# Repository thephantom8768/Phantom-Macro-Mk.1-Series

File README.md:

# Phantom Macro Mk.1 Series

> A modular, snap-together macropad ecosystem with lateral pogo-pin bus interconnects.

Chain modules side-by-side to expand your desktop workflow—from a compact macro-pad into a full fledge keyboard.

---

## 📌 Project Status

- **Hardware:** Series still in-dev
- **Case/Enclosure:** Currently only available for Pad. (Half-life week 2, its inside 3D case file)
- **Firmware:** Pad is almost complete but I need to built it to measure the adc. Others are still in-dev
- **Interconnect:** Custom edge-mount 8 pin pogo interface.

---

## ⚡ Features

- **Snap & Chain Topology:** Expand your layout horizontally by mating adjacent modules using edge-mounted pogo connectors.
- **Unified Bus Standard:** Standardized power, ground, and communication rails allow any Mk.1-series compatible module to hot-mate with the system.
- **Flexible Layouts:** Mix and match different form factors (numpads, macro clusters, encoder dials) without rerunning separate USB cables to your host machine.

## ⚠️ Build Warnings

> [!WARNING]
> **DIY Soldering Required:** This is a fully self-assembled project. It is not a plug-and-play kit and requires intermediate soldering experience.

* **Double-Sided Assembly:** Depending on the macro-pad, components might need to be soldered onto **both the top and bottom** of the PCB.

## *Mk.1 Series*

<details>
  <summary><b>🔢 Phantom-Macro-Mk.1 Pad (click here)</b></summary>
  
  ### Macro Mk.1 Pad
  
  #### Schematic

#### PCB Layout

4 Layers PCB

<div style="width: max; height: max; overflow: hidden; display: inline-block;">
  
</div>

| Front (1st layer) | Bottom (4th layer) |
| ----------------- | ------------------ |
|  |  |
|  |  |

#### PCB
| Front | Back |
| ----- | ---- |
|  |  |
|  |  |

#### Case

<table>
  <tbody>
    <tr>
      <td width="50%">
        
      </td>
      <td width="50%">
        
      </td>
    </tr>
    <tr>
      <td width="50%">
        
      </td>
      <td width="50%">
        
      </td>
    </tr>
  </tbody>
</table>

</details>

<details>
  <summary><b>🎹 Phantom-Macro-Mk.1 MIDI (click here)</b></summary>
  
  ### Macro Mk.1 MIDI
  
  #### Schematic

  #### PCB Layout 

  2 Layers PCB

  | Front | Back |
  | ----- | ----- |
  |  |  |
  |  |  |

  #### PCB
  | Front | Back |
  | ----- | ---- |
  |  |  |
  |  |  |

</details>

<details>
  <summary><b>📱 Phantom-Macro-Mk.1-Prism (click here)</b></summary>

  ### Macro Mk.1 Prism

  #### Schematic

  #### PCB Layout

  4 Layers PCB

  | Front (1st layer) | Bottom (4th layer) |
  | ----------------- | ------------------ |
  | |  |
  | |  |

  #### PCB

  | Front | Back |
  | ----- | ---- |
  | |  |
  | |  |

</details>

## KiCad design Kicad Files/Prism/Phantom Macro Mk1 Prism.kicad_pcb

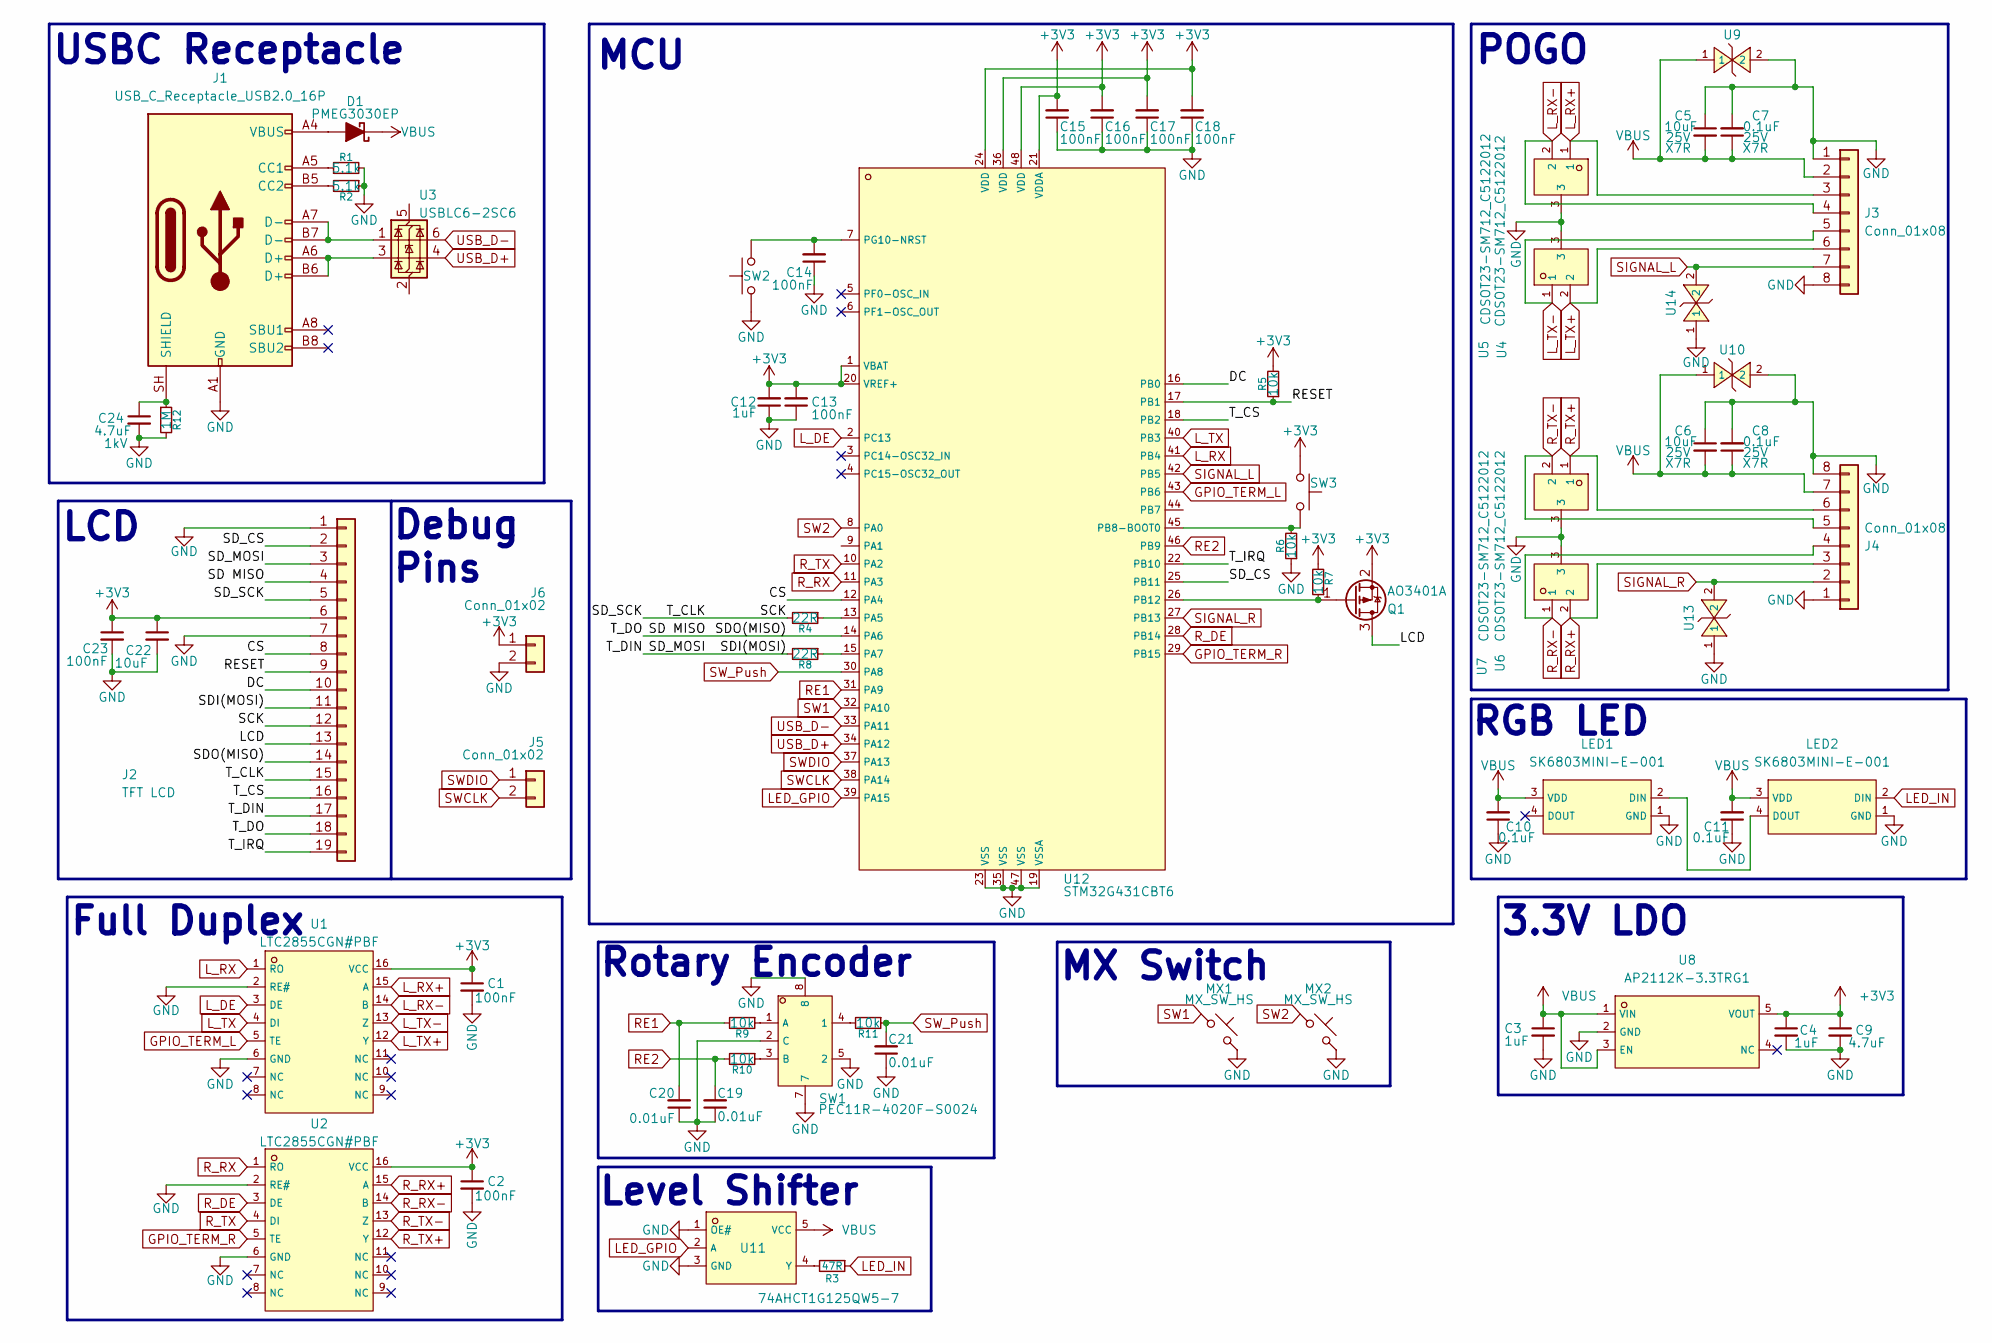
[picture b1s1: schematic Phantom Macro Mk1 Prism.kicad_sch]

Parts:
C1, C2, C13, C14, C15, C16, C17, C18: 100nF; C_0402_1005Metric_Pad0.74x0.62mm_HandSolder
C3, C4, C12: 1uF; C_0603_1608Metric_Pad1.08x0.95mm_HandSolder
C5, C6: 10uF; C_0805_2012Metric_Pad1.18x1.45mm_HandSolder; Rating 25V
C7, C8: 0.1uF; C_0805_2012Metric_Pad1.18x1.45mm_HandSolder; Rating 25V
C9, C24: 4.7uF; C_0805_2012Metric_Pad1.18x1.45mm_HandSolder
C10, C11: 0.1uF; C_0402_1005Metric_Pad0.74x0.62mm_HandSolder
C19, C20, C21: 0.01uF; C_0805_2012Metric_Pad1.18x1.45mm_HandSolder
C22: 10uF; C_0805_2012Metric_Pad1.18x1.45mm_HandSolder
C23: 100nF; C_0805_2012Metric_Pad1.18x1.45mm_HandSolder
D1: PMEG3030EP; D_SOD-128
J1: USB_C_Receptacle_USB2.0_16P; USB_C_Receptacle_GCT_USB4085
J2: TFT LCD; DLS23028B 2.8 inch SPI TFT LCD
J3, J4: Conn_01x08; PinHeader_1x08_P2.54mm_Horizontal
J5, J6: Conn_01x02; PinHeader_1x02_P2.54mm_Vertical
LED1, LED2: SK6803MINI-E-001; C5242955_LED-SMD_4P-L3_2-W2_8_SK6803MINI-E-001; LCSC C5242955
MX1, MX2: MX_SW_HS; SW_MX_HS_CPG151101S11_1u
Q1: AO3401A; SOT-23
R1, R2: 5.1k; R_0402_1005Metric_Pad0.72x0.64mm_HandSolder
R3: 47R; R_0402_1005Metric_Pad0.72x0.64mm_HandSolder
R4, R8: 22R; R_0402_1005Metric_Pad0.72x0.64mm_HandSolder
R5, R6, R7, R9, R10, R11: 10k; R_0402_1005Metric_Pad0.72x0.64mm_HandSolder
R12: 1M; R_0805_2012Metric_Pad1.20x1.40mm_HandSolder
SW1: PEC11R-4020F-S0024; C143788_SW-TH_5P-L12_5-W13_4-P2_50-LS14_5; LCSC C143788
SW2, SW3: SW_Push; SW_SPST_B3U-1000P
U1, U2: LTC2855CGN#PBF; C682796_SSOP-16_L4_9-W3_9-P0_64-LS6_0-BL; LCSC C682796
U3: USBLC6-2SC6; SOT-23-6
U4, U5, U6, U7: CDSOT23-SM712_C5122012; C5122012_SOT-23-3_L2_9-W1_3-P0_95-LS2_4-BR; LCSC C5122012
U8: AP2112K-3.3TRG1; C51118_SOT-25-5_L2_9-W1_6-P0_95-LS2_8-BL; LCSC C51118
U9, U10, U13, U14: TPD1E10B06DPYR; C48260_X1SON-2_L1_0-W0_6-P0_65-BI-1; LCSC C48260
U11: 74AHCT1G125QW5-7; C3755013_SOT-753_L3_1-W1_7-P0_95-LS3_0-BR; LCSC C3755013
U12: STM32G431CBT6; C529355_LQFP-48_L7_0-W7_0-P0_50-LS9_0-BL; LCSC C529355

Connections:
+3V3: C1.1, C2.1, C4.1, C9.1, C12.2, C13.2, C15.2, C16.2, C17.2, C18.2, C22.1, C23.1, J2.6, J6.1, Q1.2 (S), R5.2, R7.2, SW3.2, U1.16 (VCC), U2.16 (VCC), U8.5 (VOUT), U12.1 (VBAT), U12.20 (VREF+), U12.21 (VDDA), U12.24 (VDD), U12.36 (VDD), U12.48 (VDD)
/CS: J2.8, U12.12 (PA4)
/DC: J2.10, U12.16 (PB0)
/LCD: J2.13, Q1.3 (D)
/RESET: J2.9, R5.1, U12.17 (PB1)
/SCK: J2.5, J2.12, J2.15, R4.2
/SD MISO: J2.4, J2.14, J2.18, U12.14 (PA6)
/SDI(MOSI): J2.3, J2.11, J2.17, R8.2
/SD_CS: J2.2, U12.25 (PB11)
/T_CS: J2.16, U12.18 (PB2)
/T_IRQ: J2.19, U12.22 (PB10)
GND: C1.2, C2.2, C3.2, C4.2, C5.1, C6.1, C7.2, C8.2, C9.2, C10.1, C11.1, C12.1, C13.1, C14.1, C15.1, C16.1, C17.1, C18.1, C19.1, C20.1, C21.1, C22.2, C23.2, C24.2, J1.A1 (GND), J1.A12 (GND), J1.B1 (GND), J1.B12 (GND), J2.1, J2.7, J3.1, J3.8, J4.1, J4.8, J6.2, LED1.1 (GND), LED2.1 (GND), MX1.2, MX2.2, R1.2, R2.1, R6.1, R12.2, SW1.2 (C), SW1.5 (2), SW1.7, SW1.8, SW2.1, U1.2 (RE#), U1.6 (GND), U2.2 (RE#), U2.6 (GND), U4.3, U5.3, U6.3, U7.3, U8.2 (GND), U9.2, U10.2, U11.1 (OE#), U11.3 (GND), U12.19 (VSSA), U12.23 (VSS), U12.35 (VSS), U12.47 (VSS), U13.1, U14.1
GPIO_TERM_L: U1.5 (TE), U12.43 (PB6)
GPIO_TERM_R: U2.5 (TE), U12.29 (PB15)
LED_GPIO: U11.2 (A), U12.39 (PA15)
LED_IN: LED2.2 (DIN), R3.1
L_DE: U1.3 (DE), U12.2 (PC13)
L_RX: U1.1 (RO), U12.41 (PB4)
L_RX+: J3.3, U1.15 (A), U4.1
L_RX-: J3.4, U1.14 (B), U4.2
L_TX: U1.4 (DI), U12.40 (PB3)
L_TX+: J3.6, U1.12 (Y), U5.2
L_TX-: J3.5, U1.13 (Z), U5.1
unnamed: D1.2 (A), J1.A4 (VBUS), J1.A9 (VBUS), J1.B4 (VBUS), J1.B9 (VBUS)
unnamed: J1.A5 (CC1), R1.1
unnamed: J1.B5 (CC2), R2.2
unnamed: J1.A6 (D+), J1.B6 (D+), U3.3 (I/O2)
unnamed: J1.A7 (D-), J1.B7 (D-), U3.1 (I/O1)
unnamed: C24.1, J1.SH (SHIELD), R12.1
unnamed: LED1.2 (DIN), LED2.4 (DOUT)
unnamed: Q1.1 (G), R7.1, U12.26 (PB12)
unnamed: R11.2, SW1.4 (1)
unnamed: R9.1, SW1.1 (A)
unnamed: R10.1, SW1.3 (B)
unnamed: R3.2, U11.4 (Y)
unnamed: R4.1, U12.13 (PA5)
unnamed: R8.1, U12.15 (PA7)
unnamed: R6.2, SW3.1, U12.45 (PB8-BOOT0)
unnamed: C14.2, SW2.2, U12.7 (PG10-NRST)
RE1: C20.2, R9.2, U12.31 (PA9)
RE2: C19.2, R10.2, U12.46 (PB9)
R_DE: U2.3 (DE), U12.28 (PB14)
R_RX: U2.1 (RO), U12.11 (PA3)
R_RX+: J4.3, U2.15 (A), U7.2
R_RX-: J4.4, U2.14 (B), U7.1
R_TX: U2.4 (DI), U12.10 (PA2)
R_TX+: J4.6, U2.12 (Y), U6.1
R_TX-: J4.5, U2.13 (Z), U6.2
SIGNAL_L: J3.7, U12.42 (PB5), U14.2
SIGNAL_R: J4.2, U12.27 (PB13), U13.2
SW1: MX1.1, U12.32 (PA10)
SW2: MX2.1, U12.8 (PA0)
SWCLK: J5.2, U12.38 (PA14)
SWDIO: J5.1, U12.37 (PA13)
SW_Push: C21.2, R11.1, U12.30 (PA8)
USB_D+: U3.4 (I/O2), U12.34 (PA12)
USB_D-: U3.6 (I/O1), U12.33 (PA11)
VBUS: C3.1, C5.2, C6.2, C7.1, C8.1, C10.2, C11.2, D1.1 (K), J3.2, J4.7, LED1.3 (VDD), LED2.3 (VDD), U8.1 (VIN), U8.3 (EN), U9.1, U10.1, U11.5 (VCC)

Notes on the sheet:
3.3V LDO
MX Switch
POGO
USBC Receptacle
Full Duplex
MCU
Debug Pins
LCD
Rotary Encoder
RGB LED
Level Shifter

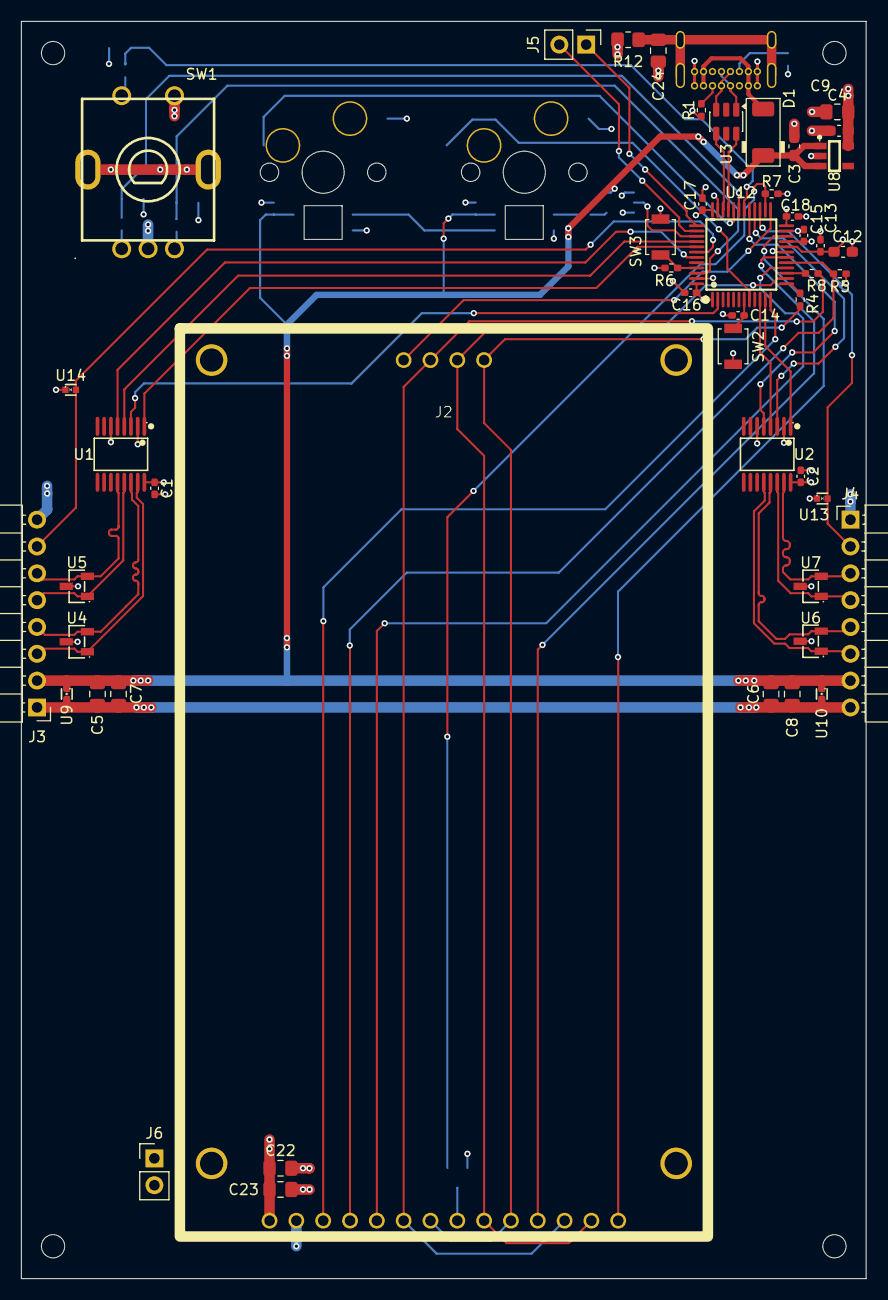
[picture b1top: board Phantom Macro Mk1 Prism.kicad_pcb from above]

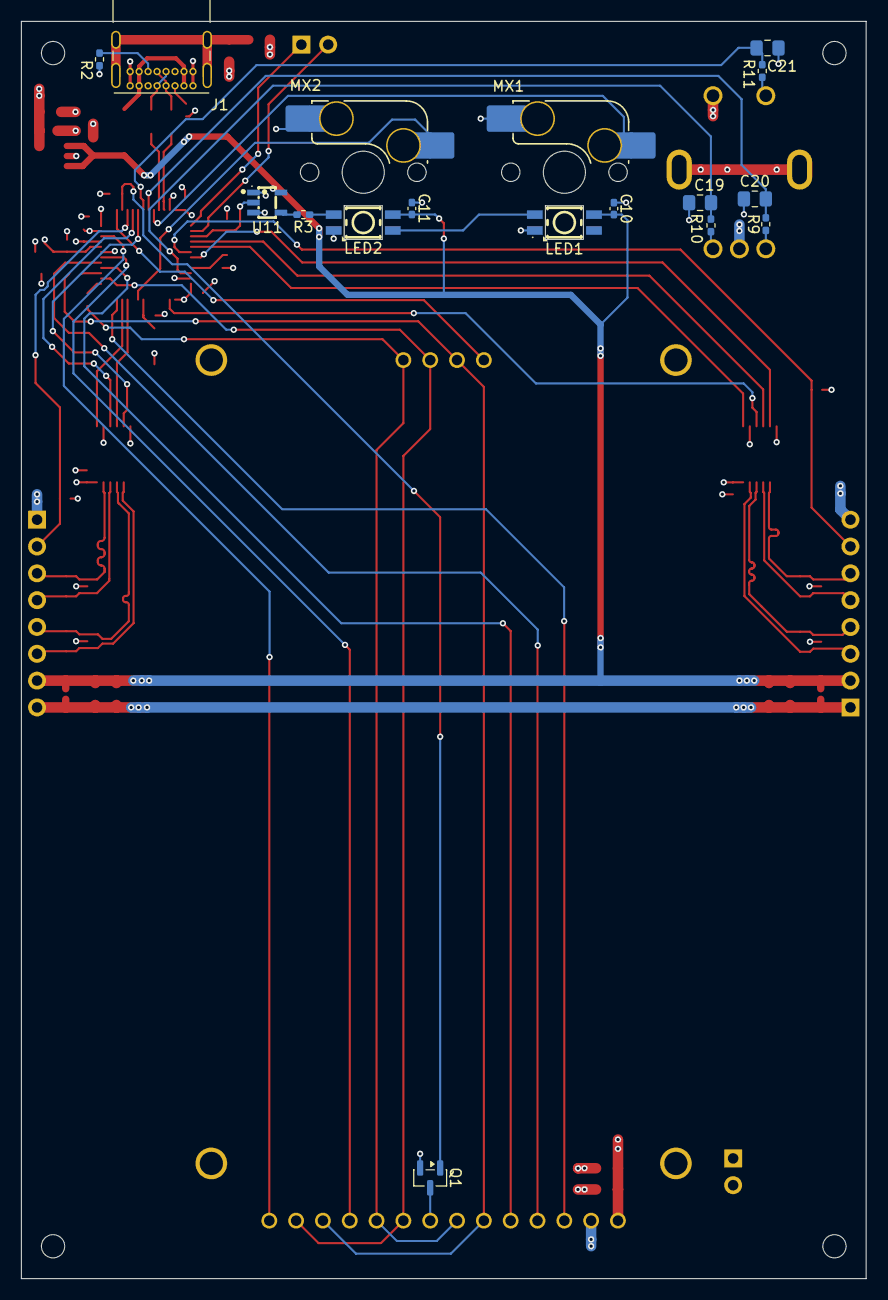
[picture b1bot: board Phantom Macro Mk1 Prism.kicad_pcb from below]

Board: 4 copper layers, 80.0 x 119.1 mm, 65 parts (17 on the bottom side), 58 nets.

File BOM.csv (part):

Phantom Macro Mk1 Pad,,,,,
Item,Qty,Supplier,Cost/item,Total Cost,link
1uF,18,TaoBao,$0.00, $0.00 ,https://item.taobao.com/item.htm?from=cart&id=630712731066&m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
0.1uF,16,TaoBao,$0.00, $0.00 ,https://item.taobao.com/item.htm?from=cart&id=731471380840&m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
100nF,8,TaoBao,$0.00, $0.00 ,https://item.taobao.com/item.htm?abbucket=0&id=733879274781&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
10uF,2,TaoBao,$0.00, $0.00 ,https://item.taobao.com/item.htm?abbucket=0&id=977236759812&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
0.1uF,2,TaoBao,$0.00, $0.00 ,https://item.taobao.com/item.htm?abbucket=0&id=730748325366&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
PMEG3030EP,1,TaoBao,$0.36, $0.36 ,https://item.taobao.com/item.htm?abbucket=20&id=694578569169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
USBLC6-2SC6,1,TaoBao,$0.23, $0.23 ,https://item.taobao.com/item.htm?id=763430084934&mi_id=0000e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
USB_C_Receptacle_USB2.0_16P,1,TaoBao,$0.08, $0.08 ,https://item.taobao.com/item.htm?id=591211481748&mi_id=0000r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
Conn_01x08,2,TaoBao,$1.04, $2.08 ,https://item.taobao.com/item.htm?ali_refid=a3_mm_12852562_17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
SK6803MINI-E-001,16,TaoBao,$0.04, $0.64 ,https://item.taobao.com/item.htm?abbucket=20&id=107449241269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
5.1k,2,TaoBao,$0.00, $0.00 ,https://item.taobao.com/item.htm?id=525633713781&mi_id=0000g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
47R,1,TaoBao,$0.00, $0.00 ,https://item.taobao.com/item.htm?id=525633713781&mi_id=0000g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
10k,1,TaoBao,$0.00, $0.00 ,https://item.taobao.com/item.htm?id=525633713781&mi_id=0000g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
PEC11R-4020F-S0024,1,TaoBao,$3.54, $3.54 ,https://item.taobao.com/item.htm?abbucket=20&id=755153501399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
SPST B3U-1000P,2,TaoBao,$0.10, $0.20 ,https://item.taobao.com/item.htm?abbucket=20&id=106190013432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
SW_MX_HE,16,Milktooth,$0.85, $13.60 ,https://milktooth.com/products/dove-he
AP2112K-3.3TRG1,1,TaoBao,$0.55, $0.55 ,https://intl.taobao.com/sk/_b.OcKv5a
CD74HC4067SM96,2,TaoBao,$0.35, $0.70 ,https://item.taobao.com/item.htm?id=659268510241&mi_id=00007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
74AHCT1G125QW5-7,1,TaoBao,$0.31, $0.31 ,https://item.taobao.com/item.htm?id=581190029859&mi_id=0000C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
STM32G431CBT6,1,TaoBao,$3.67, $3.67 ,https://item.taobao.com/item.htm?id=662218011027&mi_id=0000x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
LTC2855CGN#PBF,2,AliXpress,$8.44, $16.88 ,https://a.aliexpress.com/_c40x90oj
CDSOT23-SM712_C5122012,4,TaoBao,$0.05, $0.20 ,https://detail.tmall.com/item.htm?from=cart&id=903941269382&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
TPD1E10B06DPYR,4,TaoBao,$0.08, $0.32 ,https://item.taobao.com/item.htm?id=594637912684&mi_id=0000W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
DRV5055,16,TaoBao,$0.94, $15.04 ,https://detail.tmall.com/item.htm?from=cart&id=660549060773&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
PCB,1,JLCPCB,$29.30, $29.30 ,https://JLCPCB.com
Estimated total shipping,1,,, $7.13 ,
,,,,,
Total,,,, $117.60 ,
,,,,,
,,,,,
Phantom Macro Mk1 MIDI,,,,,
Item,Qty,Supplier,Cost/item,Total Cost link,
1uF,3,TaoBao,$0.00, $0.00 ,https://item.taobao.com/item.htm?from=cart&id=630712731066&m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
4.7uF,1,TaoBao,$0.00, $0.00 ,https://item.taobao.com/item.htm?from=cart&id=630712731066&m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
100nF,14,TaoBao,$0.00, $0.00 ,https://item.taobao.com/item.htm?abbucket=0&id=733879274781&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
0.1uF,2,TaoBao,$0.00, $0.00 ,https://item.taobao.com/item.htm?abbucket=0&id=733879274781&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
10uF,2,TaoBao,$0.00, $0.00 ,https://item.taobao.com/item.htm?from=cart&id=630712731066&m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
PMEG3030EP,1,TaoBao,$0.36, $0.36 ,https://item.taobao.com/item.htm?abbucket=20&id=694578569169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
USB_C_Receptacle_USB2.0_16P,1,TaoBao,$0.08, $0.08 ,https://item.taobao.com/item.htm?id=591211481748&mi_id=0000r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
Conn_01x08,2,TaoBao,$1.04, $2.08 ,https://item.taobao.com/item.htm?ali_refid=a3_mm_12852562_17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
SK6803MINI-E-001,4,TaoBao,$0.04, $0.16 ,https://item.taobao.com/item.htm?abbucket=20&id=107449241269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
MX_SW_HS,4,Milktooth,$6.50, $6.50 ,https://milktooth.com/products/bobagum
PTA6043-2015DPB502,4,TaoBao,$3.63, $14.52 ,https://item.taobao.com/item.htm?abbucket=20&id=903442015461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
47R,1,TaoBao,$0.00, $0.00 ,https://item.taobao.com/item.htm?id=525633713781&mi_id=0000g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
5.2k,2,TaoBao,$0.00, $0.00 ,https://item.taobao.com/item.htm?id=525633713781&mi_id=0000g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
10k,3,TaoBao,$0.00, $0.00 ,https://item.taobao.com/item.htm?id=525633713781&mi_id=0000g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
100R,1,TaoBao,$0.00, $0.00 ,https://item.taobao.com/item.htm?id=525633713781&mi_id=0000g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
4.7k,2,TaoBao,$0.00, $0.00 ,https://item.taobao.com/item.htm?id=525633713781&mi_id=0000g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
2k,12,TaoBao,$0.00, $0.00 ,https://item.taobao.com/item.htm?id=525633713781&mi_id=0000g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
PEC11R-4020F-S0024,3,TaoBao,$3.54, $3.54 ,https://item.taobao.com/item.htm?abbucket=20&id=755153501399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
SW_Push,2,TaoBao,$0.10, $0.20 ,https://item.taobao.com/item.htm?abbucket=20&id=106190013432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
MPR121QR2,1,TaoBao,$0.98, $0.98 ,https://item.taobao.com/item.htm?ali_refid=a3_430008_1006%3A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
AP2112K-3.3TRG1,1,TaoBao,$0.55, $0.55 ,https://intl.taobao.com/sk/_b.OcKv5a
USBLC6-2SC6,1,TaoBao,$0.23, $0.23 ,https://item.taobao.com/item.htm?id=763430084934&mi_id=0000e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
STM32G431RBT6,1,TaoBao,$1.54, $1.54 ,https://item.taobao.com/item.htm?abbucket=20&id=924267807464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
LTC2855CGN#PBF,2,TaoBao,$8.44, $16.88 ,https://a.aliexpress.com/_c40x90oj
CDSOT23-SM712_C5122012,4,TaoBao,$0.05, $0.20 ,https://detail.tmall.com/item.htm?from=cart&id=903941269382&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
TPD1E10B06DPYR,8,TaoBao,$0.08, $0.64 ,https://item.taobao.com/item.htm?id=594637912684&mi_id=0000W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
74AHCT1G125QW5-7,1,TaoBao,$0.31, $0.31 ,https://item.taobao.com/item.htm?id=581190029859&mi_id=0000C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
PCB,1,JLCPCB,$14.90, $14.90 ,https://JLCPCB.com
Estimated total shipping,1,,, $5.00 ,
,,,,,
Total,,,, $63.67 ,
,,,,,
,,,,,
Phantom Macro Mk1 Prism,,,,,
Item,Qty,Supplier,Cost/item,Total Cost link,
100nF,8,TaoBao,$0.00, $0.00 ,https://item.taobao.com/item.htm?abbucket=0&id=733879274781&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
1uF,3,TaoBao,$0.00, $0.00 ,https://item.taobao.com/item.htm?from=cart&id=630712731066&m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
10uF,3,TaoBao,$0.00, $0.00 ,https://item.taobao.com/item.htm?abbucket=0&id=977236759812&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
0.1uF,2,TaoBao,$0.00, $0.00 ,https://item.taobao.com/item.htm?abbucket=0&id=733879274781&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
4.7uF,2,TaoBao,$0.00, $0.00 ,https://item.taobao.com/item.htm?from=cart&id=630712731066&m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
0.1uF,2,TaoBao,$0.00, $0.00 ,https://item.taobao.com/item.htm?abbucket=0&id=733879274781&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
0.01uF,3,TaoBao,$0.00, $0.00 ,https://item.taobao.com/item.htm?abbucket=0&id=733879274781&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
100nF,1,TaoBao,$0.00, $0.00 ,https://item.taobao.com/item.htm?abbucket=0&id=733879274781&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
PMEG3030EP,1,TaoBao,$0.36,  $0.36  ,https://item.taobao.com/item.htm?abbucket=20&id=694578569169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
USB_C_Receptacle_USB2.0_16P,1,TaoBao,$0.08, $0.08 ,https://item.taobao.com/item.htm?id=591211481748&mi_id=0000r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
TFT LCD,1,Elecrow,$7.50, $7.50 ,https://www.elecrow.com/2-8-inch-320x240-spi-serial-tft-lcd-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
Conn_01x08,2,TaoBao,$1.04,  $2.08  ,https://item.taobao.com/item.htm?ali_refid=a3_mm_12852562_17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
SK6803MINI-E-001,2,TaoBao,$0.04,  $0.08 ,https://item.taobao.com/item.htm?abbucket=20&id=107449241269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
MX_SW_HS,2,Milktooth,$6.50,  $6.50  ,https://milktooth.com/products/bobagum
AO3401A,1,TaoBao,$0.03, $0.03 ,https://item.taobao.com/item.htm?ali_refid=a3_430620_1006%3A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
5.1k,2,TaoBao,$0.00, $0.00 ,https://item.taobao.com/item.htm?id=525633713781&mi_id=0000g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
47R,1,TaoBao,$0.00, $0.00 ,https://item.taobao.com/item.htm?id=525633713781&mi_id=0000g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
22R,2,TaoBao,$0.00, $0.00 ,https://item.taobao.com/item.htm?id=525633713781&mi_id=0000g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
10k,6,TaoBao,$0.00, $0.00 ,https://item.taobao.com/item.htm?id=525633713781&mi_id=0000g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
1M,1,TaoBao,$0.00, $0.00 ,https://item.taobao.com/item.htm?id=525633713781&mi_id=0000g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
PEC11R-4020F-S0024,1,TaoBao,$3.54,  $3.54  ,https://item.taobao.com/item.htm?abbucket=20&id=755153501399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
SW_Push,2,TaoBao,$0.10,  $0.20  ,https://item.taobao.com/item.htm?abbucket=20&id=106190013432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
LTC2855CGN#PBF,2,TaoBao,$8.44,  $16.88  ,https://a.aliexpress.com/_c40x90oj
USBLC6-2SC6,1,TaoBao,$0.23,  $0.23  ,https://item.taobao.com/item.htm?id=763430084934&mi_id=0000e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
CDSOT23-SM712_C5122012,4,TaoBao,$0.05,  $0.20  ,https://detail.tmall.com/item.htm?from=cart&id=903941269382&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
AP2112K-3.3TRG1,1,TaoBao,$0.55,  $0.55  ,https://intl.taobao.com/sk/_b.OcKv5a
TPD1E10B06DPYR,2,TaoBao,$0.08,  $0.16  ,https://item.taobao.com/item.htm?id=594637912684&mi_id=0000W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
74AHCT1G125QW5-7,1,TaoBao,$0.31,  $0.31  ,https://item.taobao.com/item.htm?id=581190029859&mi_id=0000C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
STM32G431CBT6,1,TaoBao,$3.67,  $3.67  ,https://item.taobao.com/item.htm?id=662218011027&mi_id=0000x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

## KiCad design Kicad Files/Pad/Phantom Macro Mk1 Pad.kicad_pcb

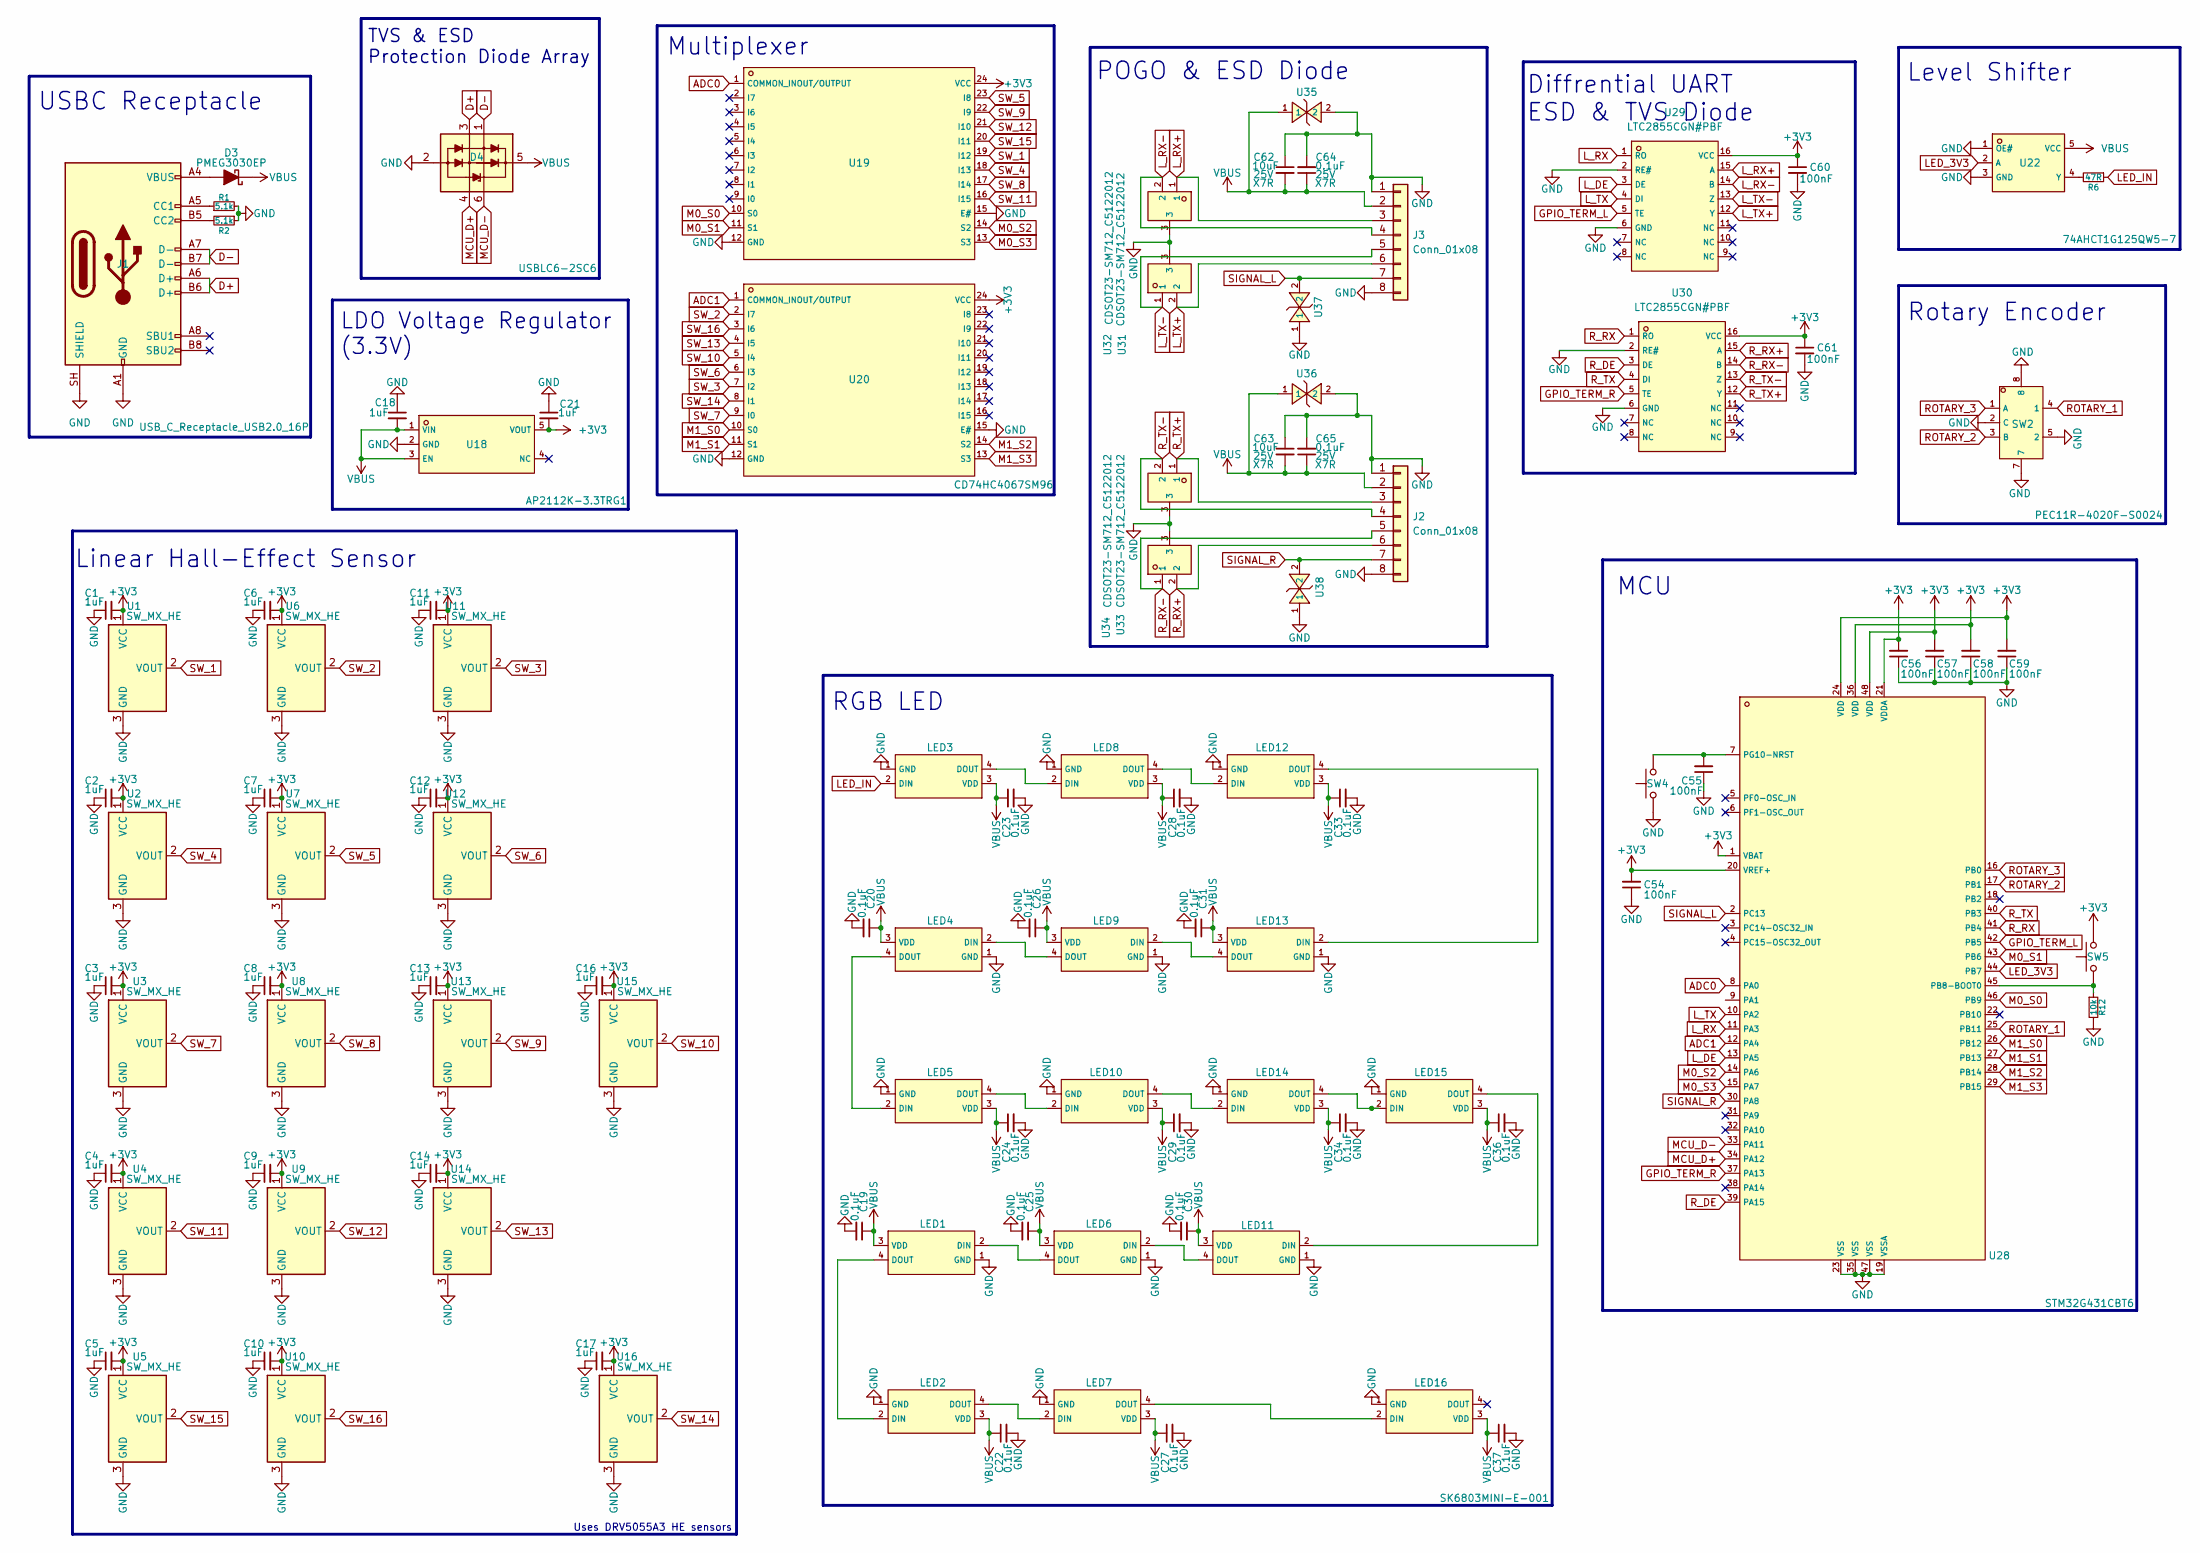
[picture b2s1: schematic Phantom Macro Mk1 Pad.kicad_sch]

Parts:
C1, C2, C3, C4, C5, C6, C7, C8, C9, C10, C11, C12, C13, C14, C16, C17, C18, C21: 1uF; C_0603_1608Metric_Pad1.08x0.95mm_HandSolder
C19, C20, C22, C23, C24, C25, C26, C27, C28, C29, C30, C31, C33, C34, C36, C37: 0.1uF; C_0603_1608Metric_Pad1.08x0.95mm_HandSolder
C54, C55, C56, C57, C58, C59, C60, C61: 100nF; C_0402_1005Metric_Pad0.74x0.62mm_HandSolder
C62, C63: 10uF; C_0805_2012Metric_Pad1.18x1.45mm_HandSolder; Rating 25V
C64, C65: 0.1uF; C_0805_2012Metric_Pad1.18x1.45mm_HandSolder; Rating 25V
D3: PMEG3030EP; D_SOD-128
D4: USBLC6-2SC6; SOT-23-6
J1: USB_C_Receptacle_USB2.0_16P; USB_C_Receptacle_GCT_USB4110
J2, J3: Conn_01x08; PinHeader_1x08_P2.54mm_Horizontal
LED1, LED2, LED3, LED4, LED5, LED6, LED7, LED8, LED9, LED10, LED11, LED12, LED13, LED14, LED15, LED16: SK6803MINI-E-001; C5242955_LED-SMD_4P-L3_2-W2_8_SK6803MINI-E-001; LCSC C5242955
R1, R2: 5.1k; R_0402_1005Metric_Pad0.72x0.64mm_HandSolder
R6: 47R; R_0402_1005Metric_Pad0.72x0.64mm_HandSolder
R12: 10k; R_0402_1005Metric_Pad0.72x0.64mm_HandSolder
SW2: PEC11R-4020F-S0024; C143788_SW-TH_5P-L12_5-W13_4-P2_50-LS14_5; LCSC C143788
SW4, SW5: SW_Push; SW_SPST_B3U-1000P
U1, U2, U3, U4, U5, U6, U7, U8, U9, U10, U11, U12, U13, U14, U15, U16: SW_MX_HE; Haimu Dove H V2
U18: AP2112K-3.3TRG1; C51118_SOT-25-5_L2_9-W1_6-P0_95-LS2_8-BL; LCSC C51118
U19, U20: CD74HC4067SM96; C98457_SSOP-24_L8_1-W5_3-P0_65-LS7_8-BL; LCSC C98457
U22: 74AHCT1G125QW5-7; C3755013_SOT-753_L3_1-W1_7-P0_95-LS3_0-BR; LCSC C3755013
U28: STM32G431CBT6; C529355_LQFP-48_L7_0-W7_0-P0_50-LS9_0-BL; LCSC C529355
U29, U30: LTC2855CGN#PBF; C682796_SSOP-16_L4_9-W3_9-P0_64-LS6_0-BL; LCSC C682796
U31, U32, U33, U34: CDSOT23-SM712_C5122012; C5122012_SOT-23-3_L2_9-W1_3-P0_95-LS2_4-BR; LCSC C5122012
U35, U36, U37, U38: TPD1E10B06DPYR; C48260_X1SON-2_L1_0-W0_6-P0_65-BI-1; LCSC C48260

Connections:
+3V3: C1.2, C2.2, C3.2, C4.2, C5.2, C6.2, C7.2, C8.2, C9.2, C10.2, C11.2, C12.2, C13.2, C14.2, C16.2, C17.2, C21.2, C54.2, C56.2, C57.2, C58.2, C59.2, C60.1, C61.1, SW5.2, U1.1 (VCC), U2.1 (VCC), U3.1 (VCC), U4.1 (VCC), U5.1 (VCC), U6.1 (VCC), U7.1 (VCC), U8.1 (VCC), U9.1 (VCC), U10.1 (VCC), U11.1 (VCC), U12.1 (VCC), U13.1 (VCC), U14.1 (VCC), U15.1 (VCC), U16.1 (VCC), U18.5 (VOUT), U19.24 (VCC), U20.24 (VCC), U28.1 (VBAT), U28.20 (VREF+), U28.21 (VDDA), U28.24 (VDD), U28.36 (VDD), U28.48 (VDD), U29.16 (VCC), U30.16 (VCC)
ADC0: U19.1 (COMMON_INOUT/OUTPUT), U28.8 (PA0)
ADC1: U20.1 (COMMON_INOUT/OUTPUT), U28.12 (PA4)
D+: D4.3 (L2), J1.A6 (D+), J1.B6 (D+)
D-: D4.1 (L1), J1.A7 (D-), J1.B7 (D-)
GND: C1.1, C2.1, C3.1, C4.1, C5.1, C6.1, C7.1, C8.1, C9.1, C10.1, C11.1, C12.1, C13.1, C14.1, C16.1, C17.1, C18.1, C19.2, C20.2, C21.1, C22.2, C23.2, C24.2, C25.2, C26.2, C27.2, C28.2, C29.2, C30.2, C31.2, C33.2, C34.2, C36.2, C37.2, C54.1, C55.1, C56.1, C57.1, C58.1, C59.1, C60.2, C61.2, C62.1, C63.1, C64.2, C65.2, D4.2 (VN), J1.A1 (GND), J1.A12 (GND), J1.B1 (GND), J1.B12 (GND), J1.SH (SHIELD), J2.1, J2.8, J3.1, J3.8, LED1.1 (GND), LED2.1 (GND), LED3.1 (GND), LED4.1 (GND), LED5.1 (GND), LED6.1 (GND), LED7.1 (GND), LED8.1 (GND), LED9.1 (GND), LED10.1 (GND), LED11.1 (GND), LED12.1 (GND), LED13.1 (GND), LED14.1 (GND), LED15.1 (GND), LED16.1 (GND), R1.2, R2.1, R12.2, SW2.2 (C), SW2.5 (2), SW2.7, SW2.8, SW4.1, U1.3 (GND), U2.3 (GND), U3.3 (GND), U4.3 (GND), U5.3 (GND), U6.3 (GND), U7.3 (GND), U8.3 (GND), U9.3 (GND), U10.3 (GND), U11.3 (GND), U12.3 (GND), U13.3 (GND), U14.3 (GND), U15.3 (GND), U16.3 (GND), U18.2 (GND), U19.12 (GND), U19.15 (E#), U20.12 (GND), U20.15 (E#), U22.1 (OE#), U22.3 (GND), U28.19 (VSSA), U28.23 (VSS), U28.35 (VSS), U28.47 (VSS), U29.2 (RE#), U29.6 (GND), U30.2 (RE#), U30.6 (GND), U31.3, U32.3, U33.3, U34.3, U35.2, U36.2, U37.1, U38.1
GPIO_TERM_L: U28.42 (PB5), U29.5 (TE)
GPIO_TERM_R: U28.37 (PA13), U30.5 (TE)
LED_3V3: U22.2 (A), U28.44 (PB7)
LED_IN: LED3.2 (DIN), R6.1
L_DE: U28.13 (PA5), U29.3 (DE)
L_RX: U28.11 (PA3), U29.1 (RO)
L_RX+: J3.3, U29.15 (A), U31.1
L_RX-: J3.4, U29.14 (B), U31.2
L_TX: U28.10 (PA2), U29.4 (DI)
L_TX+: J3.6, U29.12 (Y), U32.2
L_TX-: J3.5, U29.13 (Z), U32.1
M0_S0: U19.10 (S0), U28.46 (PB9)
M0_S1: U19.11 (S1), U28.43 (PB6)
M0_S2: U19.14 (S2), U28.14 (PA6)
M0_S3: U19.13 (S3), U28.15 (PA7)
M1_S0: U20.10 (S0), U28.26 (PB12)
M1_S1: U20.11 (S1), U28.27 (PB13)
M1_S2: U20.14 (S2), U28.28 (PB14)
M1_S3: U20.13 (S3), U28.29 (PB15)
MCU_D+: D4.4 (L2), U28.34 (PA12)
MCU_D-: D4.6 (L1), U28.33 (PA11)
unnamed: D3.2 (A), J1.A4 (VBUS), J1.A9 (VBUS), J1.B4 (VBUS), J1.B9 (VBUS)
unnamed: J1.A5 (CC1), R1.1
unnamed: J1.B5 (CC2), R2.2
unnamed: LED1.2 (DIN), LED6.4 (DOUT)
unnamed: LED1.4 (DOUT), LED2.2 (DIN)
unnamed: LED2.4 (DOUT), LED7.2 (DIN)
unnamed: LED3.4 (DOUT), LED8.2 (DIN)
unnamed: LED4.2 (DIN), LED9.4 (DOUT)
unnamed: LED4.4 (DOUT), LED5.2 (DIN)
unnamed: LED5.4 (DOUT), LED10.2 (DIN)
unnamed: LED10.4 (DOUT), LED14.2 (DIN)
unnamed: LED11.2 (DIN), LED15.4 (DOUT)
unnamed: LED6.2 (DIN), LED11.4 (DOUT)
unnamed: LED8.4 (DOUT), LED12.2 (DIN)
unnamed: LED12.4 (DOUT), LED13.2 (DIN)
unnamed: LED9.2 (DIN), LED13.4 (DOUT)
unnamed: LED14.4 (DOUT), LED15.2 (DIN)
unnamed: LED7.4 (DOUT), LED16.2 (DIN)
unnamed: R6.2, U22.4 (Y)
unnamed: R12.1, SW5.1, U28.45 (PB8-BOOT0)
unnamed: C55.2, SW4.2, U28.7 (PG10-NRST)
ROTARY_1: SW2.4 (1), U28.25 (PB11)
ROTARY_2: SW2.3 (B), U28.17 (PB1)
ROTARY_3: SW2.1 (A), U28.16 (PB0)
R_DE: U28.39 (PA15), U30.3 (DE)
R_RX: U28.41 (PB4), U30.1 (RO)
R_RX+: J2.6, U30.15 (A), U34.2
R_RX-: J2.5, U30.14 (B), U34.1
R_TX: U28.40 (PB3), U30.4 (DI)
R_TX+: J2.3, U30.12 (Y), U33.1
R_TX-: J2.4, U30.13 (Z), U33.2
SIGNAL_L: J3.7, U28.2 (PC13), U37.2
SIGNAL_R: J2.7, U28.30 (PA8), U38.2
SW_1: U1.2 (VOUT), U19.19 (I12)
SW_2: U6.2 (VOUT), U20.2 (I7)
SW_3: U11.2 (VOUT), U20.7 (I2)
SW_4: U2.2 (VOUT), U19.18 (I13)
SW_5: U7.2 (VOUT), U19.23 (I8)
SW_6: U12.2 (VOUT), U20.6 (I3)
SW_7: U3.2 (VOUT), U20.9 (I0)
SW_8: U8.2 (VOUT), U19.17 (I14)
SW_9: U13.2 (VOUT), U19.22 (I9)
SW_10: U15.2 (VOUT), U20.5 (I4)
SW_11: U4.2 (VOUT), U19.16 (I15)
SW_12: U9.2 (VOUT), U19.21 (I10)
SW_13: U14.2 (VOUT), U20.4 (I5)
SW_14: U16.2 (VOUT), U20.8 (I1)
SW_15: U5.2 (VOUT), U19.20 (I11)
SW_16: U10.2 (VOUT), U20.3 (I6)
VBUS: C18.2, C19.1, C20.1, C22.1, C23.1, C24.1, C25.1, C26.1, C27.1, C28.1, C29.1, C30.1, C31.1, C33.1, C34.1, C36.1, C37.1, C62.2, C63.2, C64.1, C65.1, D3.1 (K), D4.5 (VP), J2.2, J3.2, LED1.3 (VDD), LED2.3 (VDD), LED3.3 (VDD), LED4.3 (VDD), LED5.3 (VDD), LED6.3 (VDD), LED7.3 (VDD), LED8.3 (VDD), LED9.3 (VDD), LED10.3 (VDD), LED11.3 (VDD), LED12.3 (VDD), LED13.3 (VDD), LED14.3 (VDD), LED15.3 (VDD), LED16.3 (VDD), U18.1 (VIN), U18.3 (EN), U22.5 (VCC), U35.1, U36.1

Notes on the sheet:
LDO Voltage Regulator (3.3V)
RGB LED
Multiplexer
Level Shifter
MCU
Rotary Encoder
TVS & ESD Protection Diode Array
Uses DRV5055A3 HE sensors
Linear Hall-Effect Sensor
POGO & ESD Diode
Diffrential UART ESD & TVS Diode
USBC Receptacle

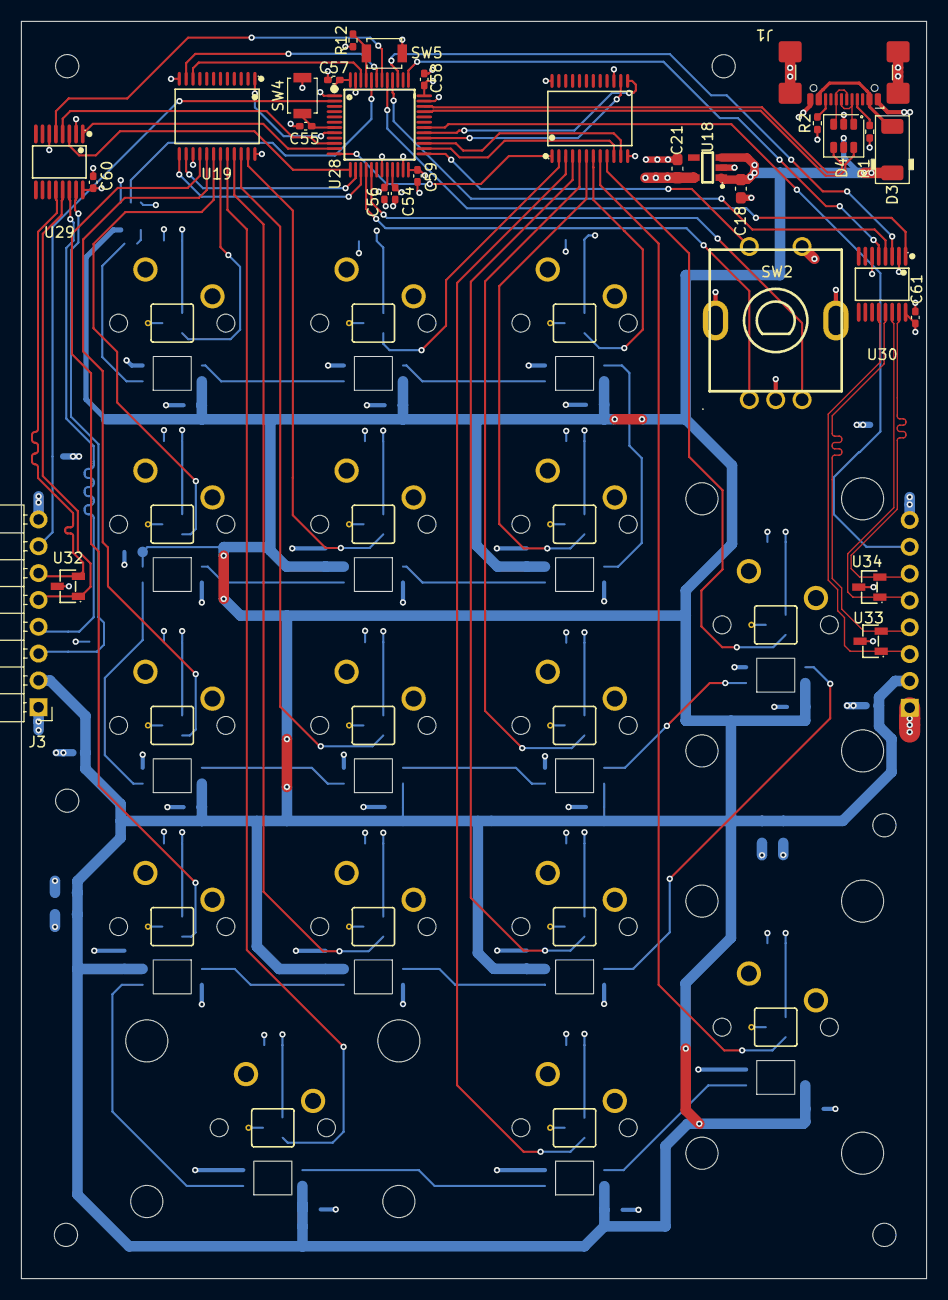
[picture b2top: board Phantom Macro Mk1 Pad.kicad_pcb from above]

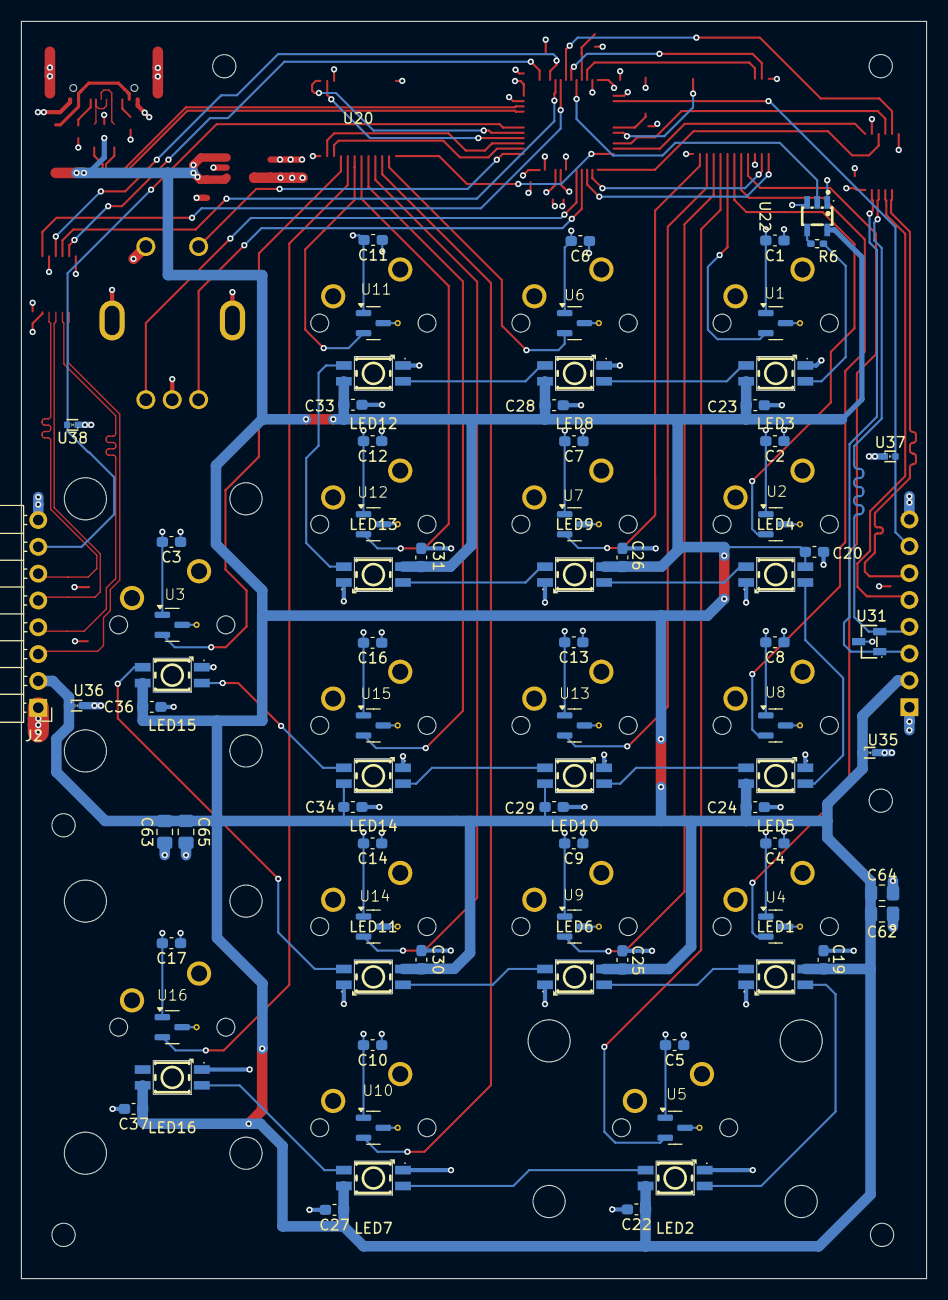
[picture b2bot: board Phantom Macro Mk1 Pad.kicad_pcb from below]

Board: 4 copper layers, 85.7 x 119.1 mm, 105 parts (76 on the bottom side), 77 nets.
